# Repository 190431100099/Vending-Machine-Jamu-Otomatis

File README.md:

# 🥤 Vending Machine Jamu Otomatis

An automated herbal drink (Jamu) vending machine built with **Arduino Mega**. This machine allows users to select from 5 different types of Jamu and choose their preferred water temperature (Cold, Warm, or Hot). It features a coin-operated system, precise liquid dispensing using flow sensors, and safety detection using ultrasonic sensors.

## 🌟 Features

- **5 Varieties of Jamu:** Selectable via push buttons.
- **Temperature Control:** Options for Cold (Dingin), Warm (Hangat), and Hot (Panas) water.
- **Coin System:** Accepts coins via a coin acceptor (Pulse counting).
- **Precision Dispensing:** Uses a flow sensor to measure and dispense the exact volume (20ml Jamu + 180ml Water).
- **Safety Sensor:** Ultrasonic sensor ensures a cup is placed before dispensing liquid.
- **LCD Interface:** 20x4 I2C LCD to guide users through the transaction process.

## ⚙️ Hardware Components

- **Microcontroller:** Arduino Mega
- **Display:** LCD 20x4 with I2C module
- **Sensors:**
  - Ultrasonic Sensor (HC-SR04) - Cup detection
  - Flow Sensor (YF-S201) - Liquid volume measurement
  - Coin Acceptor - Payment input
- **Actuators:**
  - 5x Relay Modules (for Jamu pumps)
  - 2x Relay Modules (for Hot and Cold water solenoids/pumps)
- **Input:** 8x Push Buttons (Selection & Temp)

## 📂 Repository Structure

```
.
├── Vending_Machine_Jamu.ino   # Main Arduino Mega source code
├── dispenser/                 # Folder containing 3D design files (STL, etc.)
├── wiring1.sch                # Eagle schematic file (Wiring diagram)
└── README.md                  # Project documentation
```

## 🔌 Wiring

The hardware wiring connections are documented in the `wiring1.sch` file included in this repository.

**Pin Configuration Summary (based on code):**
- **Ultrasonic:** Trig `A1`, Echo `A0`
- **Relays (Jamu):** Pins `23, 24, 25, 26, 27`
- **Relays (Water):** Hot `28`, Cold `29`
- **Flow Sensor:** Pin `18` (Interrupt)
- **Coin Acceptor:** Pin `3` (Interrupt)
- **Buttons:** Pins `4, 5, 6, 7, 8` (Jamu), `9, 10, 11` (Temp)

## 🚀 How It Works

The system operates in the following sequence:

1.  **Payment:** User inserts coins. The price is set to **5 coins** per cup.
2.  **Selection:**
    -   Select Jamu type (Button 1-5).
    -   Select Water Temperature (Cold/Warm/Hot).
3.  **Detection:** User must place a cup in the dispensing area. The ultrasonic sensor detects the cup if the distance is < 9cm.
4.  **Dispensing:**
    -   The machine dispenses **20ml** of the selected Jamu concentrate.
    -   It then dispenses **180ml** of water at the selected temperature.
    -   Total volume per cup: **200ml**.
5.  **Completion:** The system resets credit and prepares for the next order.

## 🛠️ Development

This project was developed to modernize the way traditional Jamu is distributed, combining traditional heritage with modern IoT and automation technology.

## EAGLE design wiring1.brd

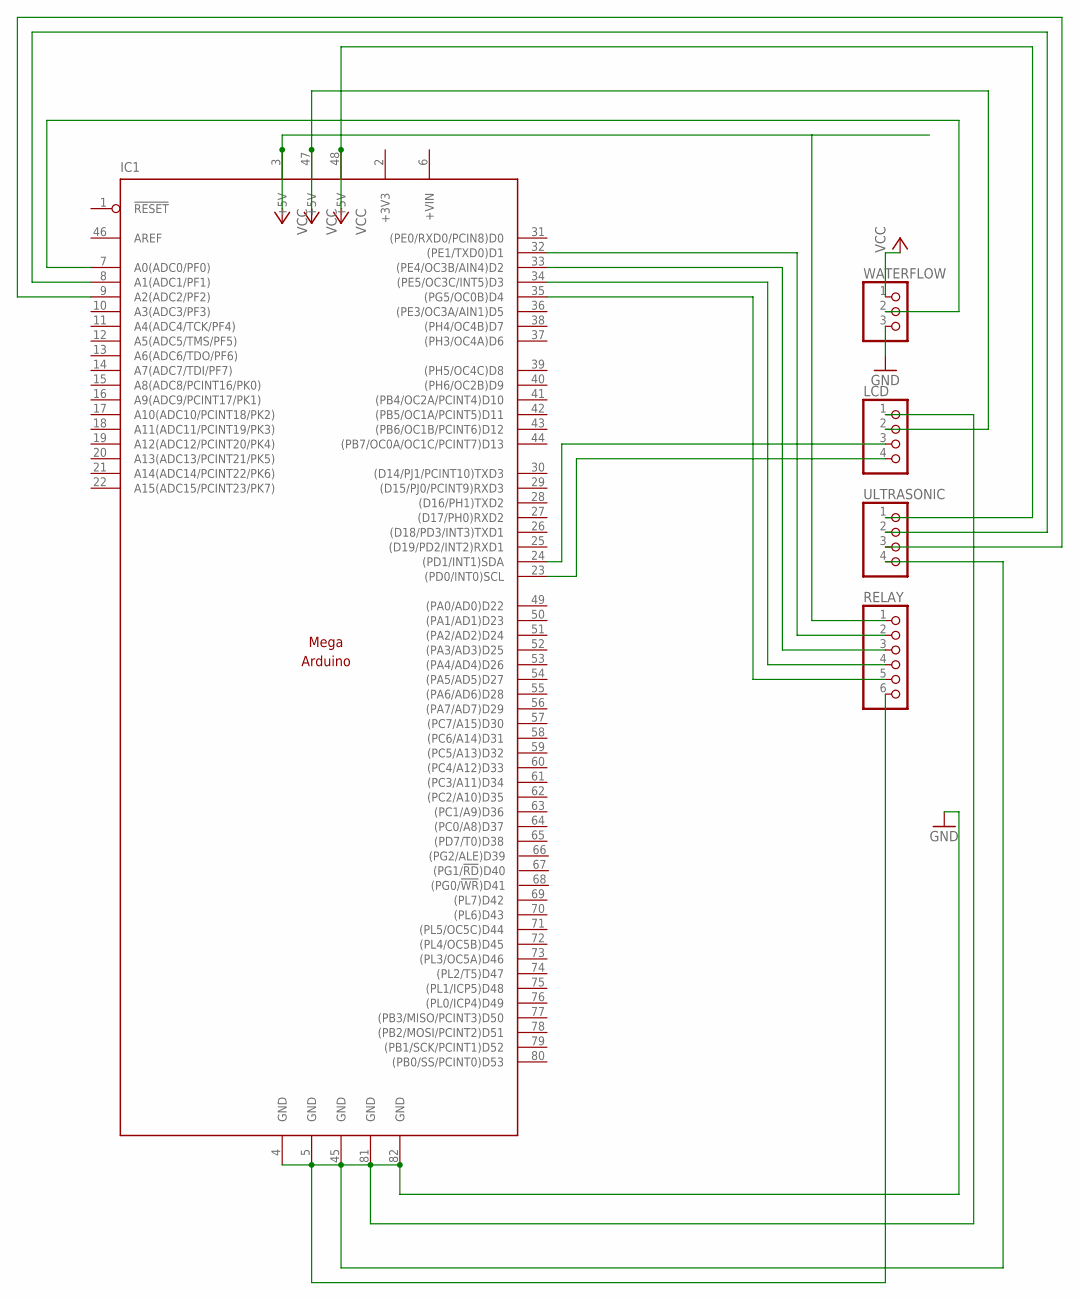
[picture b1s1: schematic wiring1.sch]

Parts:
IC1: ARDUINOMEGA
LCD: PINHD-1X4; 1X04
RELAY: PINHD-1X6; 1X06
ULTRASONIC: PINHD-1X4; 1X04
WATERFLOW: PINHD-1X3; 1X03

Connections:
+3V3: IC1.2 (+3V3)
+VIN: IC1.6 (+VIN)
GND: IC1.4 (GND), IC1.5 (GND), IC1.45 (GND), IC1.81 (GND), IC1.82 (GND), LCD.1, RELAY.6, ULTRASONIC.4, WATERFLOW.3
unnamed: IC1.9 (A2(ADC2/PF2)), ULTRASONIC.3
unnamed: IC1.8 (A1(ADC1/PF1)), ULTRASONIC.2
unnamed: IC1.24 ((PD1/INT1)SDA), LCD.3
unnamed: IC1.23 ((PD0/INT0)SCL), LCD.4
unnamed: IC1.33 ((PE4/OC3B/AIN4)D2), RELAY.3
unnamed: IC1.32 ((PE1/TXD0)D1), RELAY.2
unnamed: IC1.34 ((PE5/OC3C/INT5)D3), RELAY.4
unnamed: IC1.35 ((PG5/OC0B)D4), RELAY.5
unnamed: IC1.7 (A0(ADC0/PF0)), WATERFLOW.2
VCC: IC1.3 (+5V), IC1.47 (+5V), IC1.48 (+5V), LCD.2, RELAY.1, ULTRASONIC.1, WATERFLOW.1

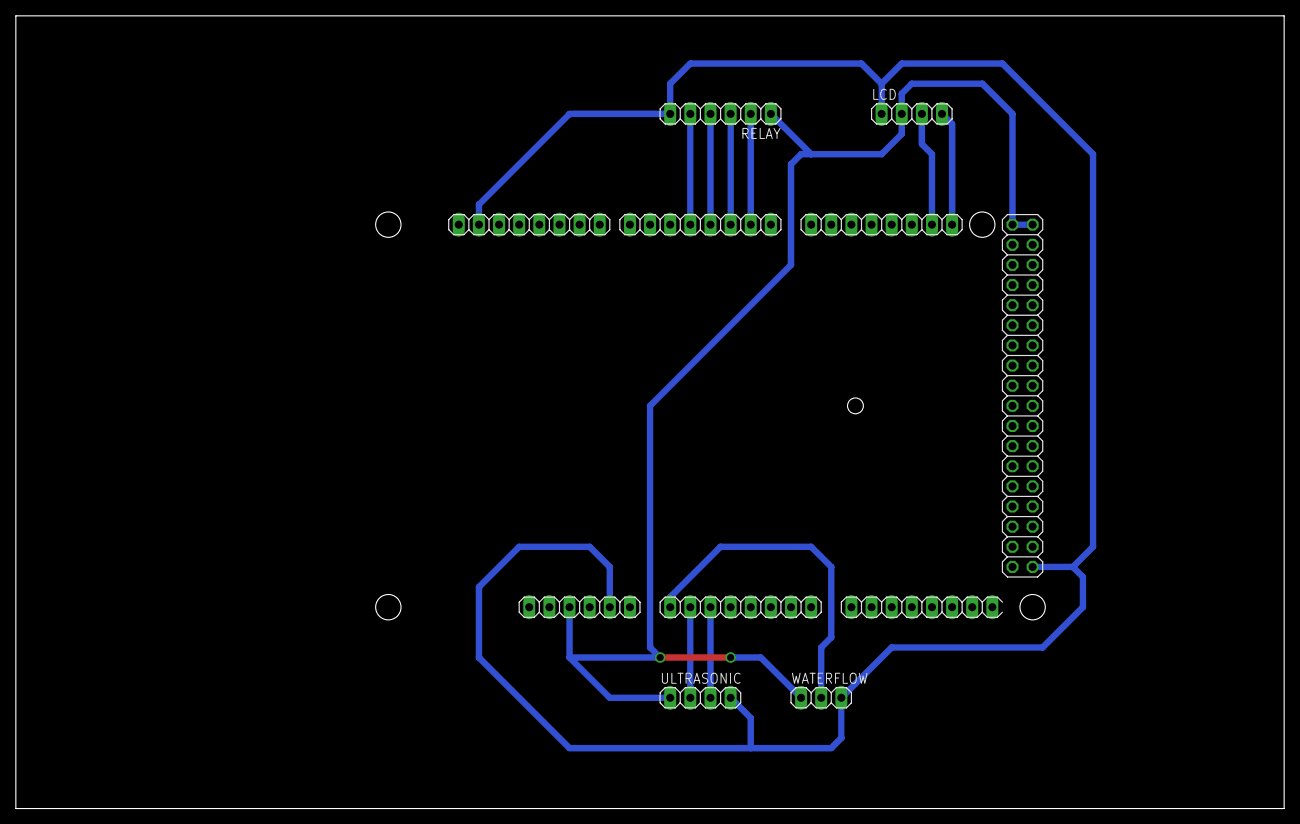
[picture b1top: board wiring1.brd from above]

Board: 2 copper layers, 160.0 x 100.0 mm, 5 parts (0 on the bottom side), 11 nets.
